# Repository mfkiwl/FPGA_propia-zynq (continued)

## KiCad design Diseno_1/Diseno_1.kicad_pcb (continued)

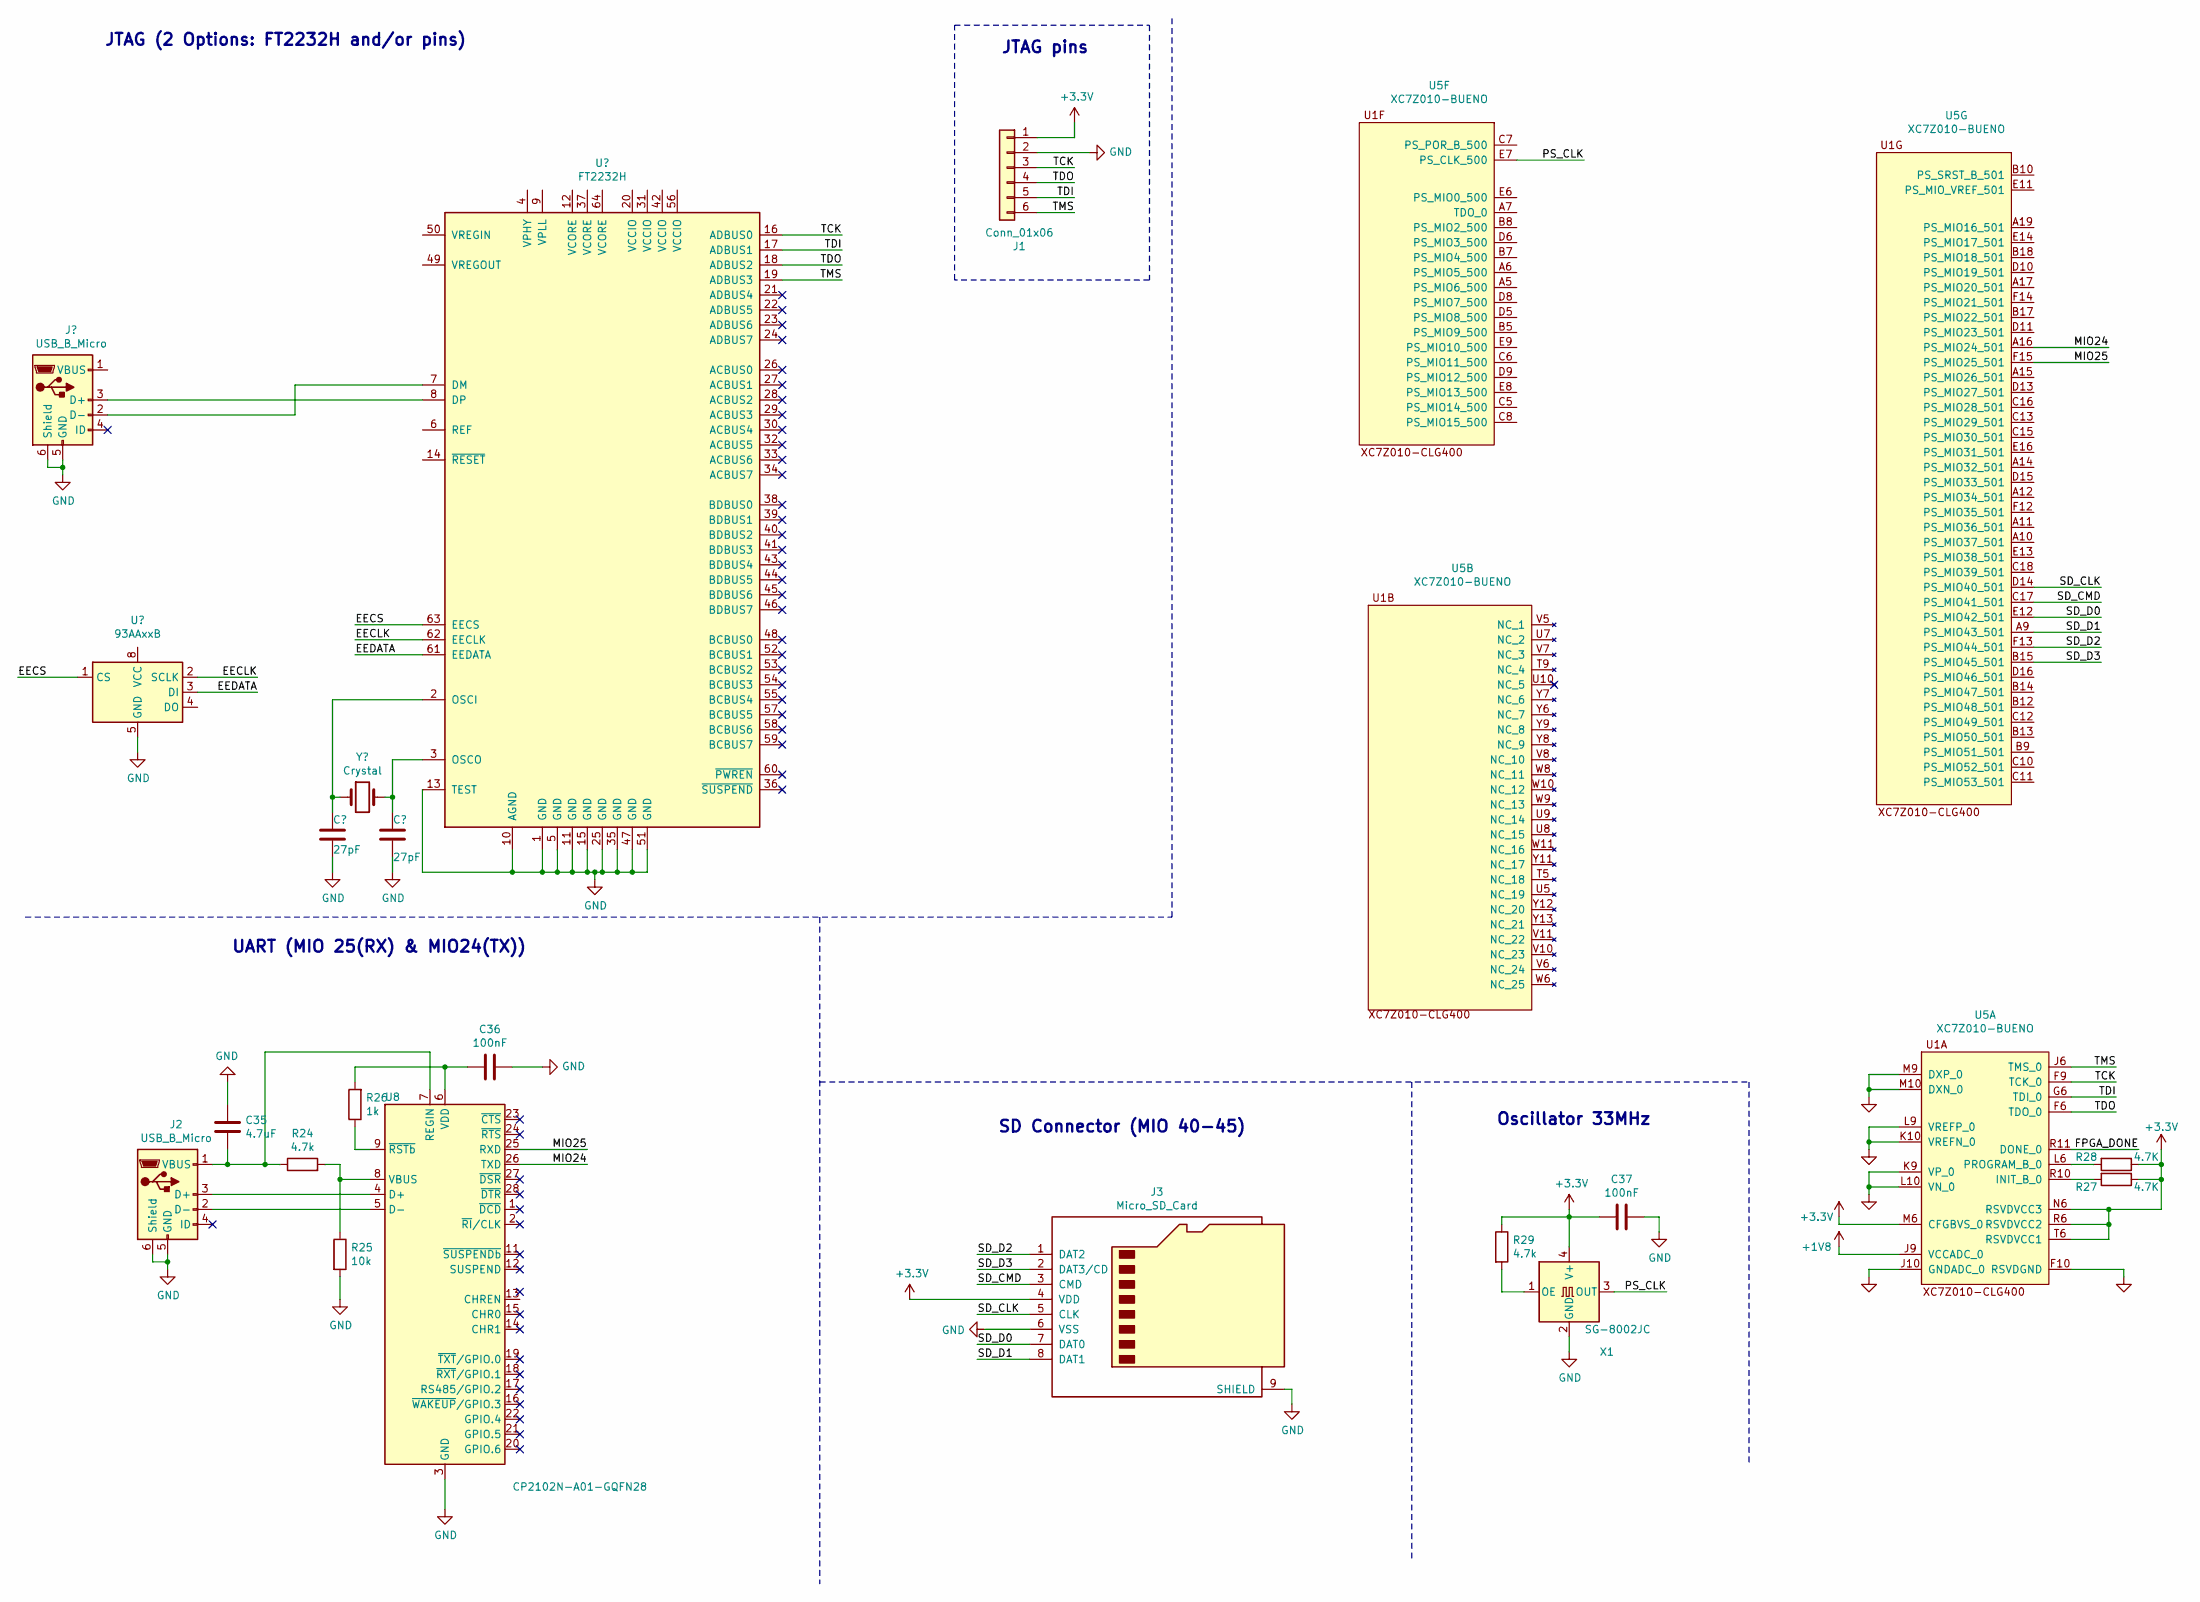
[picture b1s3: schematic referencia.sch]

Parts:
C35: 4.7uF; R_0805_2012Metric
C36: 100nF; R_0805_2012Metric
C37: 100nF; C_0805_2012Metric
J1: Conn_01x06; PinHeader_1x06_P2.54mm_Vertical
J2: USB_B_Micro; USB_Mini-B_Lumberg_2486_01_Horizontal
J3: Micro_SD_Card; microSD_HC_Wuerth_693072010801
R24, R29: 4.7k; R_0805_2012Metric
R25: 10k; R_0805_2012Metric
R26: 1k; R_0805_2012Metric
R27, R28: 4.7K; R_0805_2012Metric
U5: XC7Z010-BUENO; BGA-400_20x20_17.0x17.0mm
U8: CP2102N-A01-GQFN28; QFN-28-1EP_5x5mm_P0.5mm_EP3.35x3.35mm
X1: SG-8002JC; Oscillator_SMD_SeikoEpson_SG8002JC-4Pin_10.5x5.0mm

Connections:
+1V8: U5.J9 (VCCADC_0); also elsewhere on the board
/Entradas y Salidas/BANK34_N17: U5.N17 (IO_L23P_T3_34); also elsewhere on the board
/Entradas y Salidas/BANK34_N18: U5.N18 (IO_L13P_T2_MRCC_34); also elsewhere on the board
/Entradas y Salidas/BANK34_N20: U5.N20 (IO_L14P_T2_SRCC_34); also elsewhere on the board
/Entradas y Salidas/BANK34_P14: U5.P14 (IO_L6P_T0_34); also elsewhere on the board
/Entradas y Salidas/BANK34_P15: U5.P15 (IO_L24P_T3_34); also elsewhere on the board
/Entradas y Salidas/BANK34_P16: U5.P16 (IO_L24N_T3_34); also elsewhere on the board
/Entradas y Salidas/BANK34_P18: U5.P18 (IO_L23N_T3_34); also elsewhere on the board
/Entradas y Salidas/BANK34_P19: U5.P19 (IO_L13N_T2_MRCC_34); also elsewhere on the board
/Entradas y Salidas/BANK34_P20: U5.P20 (IO_L14N_T2_SRCC_34); also elsewhere on the board
/Entradas y Salidas/BANK34_R14: U5.R14 (IO_L6N_T0_VREF_34); also elsewhere on the board
/Entradas y Salidas/BANK34_R16: U5.R16 (IO_L19P_T3_34); also elsewhere on the board
/Entradas y Salidas/BANK34_R17: U5.R17 (IO_L19N_T3_VREF_34); also elsewhere on the board
/Entradas y Salidas/BANK34_R18: U5.R18 (IO_L20N_T3_34); also elsewhere on the board
/Entradas y Salidas/BANK34_R19: U5.R19 (IO_0_34); also elsewhere on the board
/Entradas y Salidas/BANK34_T10: U5.T10 (IO_L1N_0_34); also elsewhere on the board
/Entradas y Salidas/BANK34_T11: U5.T11 (IO_L1P_T0_34); also elsewhere on the board
/Entradas y Salidas/BANK34_T12: U5.T12 (IO_L2P_T0_34); also elsewhere on the board
/Entradas y Salidas/BANK34_T14: U5.T14 (IO_l5P_T0_34); also elsewhere on the board
/Entradas y Salidas/BANK34_T15: U5.T15 (IO_L5N_T0_34); also elsewhere on the board
/Entradas y Salidas/BANK34_T16: U5.T16 (IO_L9P_T1_DQS_34); also elsewhere on the board
/Entradas y Salidas/BANK34_T17: U5.T17 (IO_L20P_T3_34); also elsewhere on the board
/Entradas y Salidas/BANK34_T19: U5.T19 (IO_25_34); also elsewhere on the board
/Entradas y Salidas/BANK34_T20: U5.T20 (IO_L15P_T2_DQS_34); also elsewhere on the board
/Entradas y Salidas/BANK34_U12: U5.U12 (IO_L2N_T0_34); also elsewhere on the board
/Entradas y Salidas/BANK34_U14: U5.U14 (IO_L11P_T1_SRCC_34); also elsewhere on the board
/Entradas y Salidas/BANK34_U15: U5.U15 (IO_L11N_T1_SRCC_34); also elsewhere on the board
/Entradas y Salidas/BANK34_U17: U5.U17 (IO_L9N_T1_DQS_34); also elsewhere on the board
/Entradas y Salidas/BANK34_U18: U5.U18 (IO_L12P_T1_MRCC_34); also elsewhere on the board
/Entradas y Salidas/BANK34_U19: U5.U19 (IO_L12N_T1_MRCC_34); also elsewhere on the board
/Entradas y Salidas/BANK34_U20: U5.U20 (IO_L5N_T2_DQS_34); also elsewhere on the board
/Entradas y Salidas/BANK34_V12: U5.V12 (IO_L4P_T0_34); also elsewhere on the board
/Entradas y Salidas/BANK34_V13: U5.V13 (IO_L3N_T0_DQS_34); also elsewhere on the board
/Entradas y Salidas/BANK34_V15: U5.V15 (IO_L10P_T1_34); also elsewhere on the board
/Entradas y Salidas/BANK34_V16: U5.V16 (IO_L18P_T2_34); also elsewhere on the board
/Entradas y Salidas/BANK34_V17: U5.V17 (IO_L21P_T3_VREF_34); also elsewhere on the board
/Entradas y Salidas/BANK34_V18: U5.V18 (IO_L21N_T3_DQS_34); also elsewhere on the board
/Entradas y Salidas/BANK34_V20: U5.V20 (IO_L6P_T2_34); also elsewhere on the board
/Entradas y Salidas/BANK34_W13: U5.W13 (IO_L4N_T0_34); also elsewhere on the board
/Entradas y Salidas/BANK34_W14: U5.W14 (IO_L8P_T1_34); also elsewhere on the board
/Entradas y Salidas/BANK34_W15: U5.W15 (IO_L10N_T1_34); also elsewhere on the board
/Entradas y Salidas/BANK34_W16: U5.W16 (IO_L18N_T2_34); also elsewhere on the board
/Entradas y Salidas/BANK34_W18: U5.W18 (IO_L22P_T3_34); also elsewhere on the board
/Entradas y Salidas/BANK34_W19: U5.W19 (IO_L22N_T3_34); also elsewhere on the board
/Entradas y Salidas/BANK34_W20: U5.W20 (IO_L6N_T2_34); also elsewhere on the board
/Entradas y Salidas/BANK34_Y14: U5.Y14 (IO_L8N_T1_34); also elsewhere on the board
/Entradas y Salidas/BANK34_Y16: U5.Y16 (IO_L7P_T1_34); also elsewhere on the board
/Entradas y Salidas/BANK34_Y17: U5.Y17 (IO_L7N_T1_34); also elsewhere on the board
/Entradas y Salidas/BANK34_Y18: U5.Y18 (IO_L17P_T2_34); also elsewhere on the board
/Entradas y Salidas/BANK34_Y19: U5.Y19 (IO_L17N_T2_34); also elsewhere on the board
/Entradas y Salidas/BANK35_A20: U5.A20 (IO_L2N_T0_AD8N_35); also elsewhere on the board
/Entradas y Salidas/BANK35_B19: U5.B19 (IO_L2P_T0_AD8P_35); also elsewhere on the board
/Entradas y Salidas/BANK35_B20: U5.B20 (IO_L1N_T0_AD0P_35); also elsewhere on the board
/Entradas y Salidas/BANK35_C20: U5.C20 (IO_L1P_T0_AD0P_35); also elsewhere on the board
/Entradas y Salidas/BANK35_D18: U5.D18 (IO_L3N_T0_DQS_AD1N_35); also elsewhere on the board
/Entradas y Salidas/BANK35_D19: U5.D19 (IO_L4P_T0_35); also elsewhere on the board
/Entradas y Salidas/BANK35_D20: U5.D20 (IO_L4N_T0_35); also elsewhere on the board
/Entradas y Salidas/BANK35_E17: U5.E17 (IO_L3P_T0_DQS_AD1P_35); also elsewhere on the board
/Entradas y Salidas/BANK35_E18: U5.E18 (IO_L5P_T0_AD9P_35); also elsewhere on the board
/Entradas y Salidas/BANK35_E19: U5.E19 (IO_L5N_T0_AD9N_35); also elsewhere on the board
/Entradas y Salidas/BANK35_F16: U5.F16 (IO_L6P_T0_35); also elsewhere on the board
/Entradas y Salidas/BANK35_F17: U5.F17 (IO_L6N_T0_VREF_35); also elsewhere on the board
/Entradas y Salidas/BANK35_F19: U5.F19 (IO_L15P_T2_DQS_AD12P_35); also elsewhere on the board
/Entradas y Salidas/BANK35_F20: U5.F20 (IO_L15N_T2_DQS_AD12N_35); also elsewhere on the board
/Entradas y Salidas/BANK35_G14: U5.G14 (IO_0_35); also elsewhere on the board
/Entradas y Salidas/BANK35_G15: U5.G15 (IO_L19N_T3_VREF_35); also elsewhere on the board
/Entradas y Salidas/BANK35_G17: U5.G17 (IO_L16P_T2_35); also elsewhere on the board
/Entradas y Salidas/BANK35_G18: U5.G18 (IO_L16N_T2_35); also elsewhere on the board
/Entradas y Salidas/BANK35_G19: U5.G19 (IO_L18P_T2_AD13P_35); also elsewhere on the board
/Entradas y Salidas/BANK35_G20: U5.G20 (IO_L18N_T2_AD13N_35); also elsewhere on the board
/Entradas y Salidas/BANK35_H15: U5.H15 (IO_L19P_T3_35); also elsewhere on the board
/Entradas y Salidas/BANK35_H16: U5.H16 (IO_L13P_T2_MRCC_35); also elsewhere on the board
/Entradas y Salidas/BANK35_H17: U5.H17 (IO_L13N_T2_MRCC_35); also elsewhere on the board
/Entradas y Salidas/BANK35_H18: U5.H18 (IO_L14N_T2_AD4N_SRCC_35); also elsewhere on the board
/Entradas y Salidas/BANK35_H20: U5.H20 (IO_L17N_T2_AD5N_35); also elsewhere on the board
/Entradas y Salidas/BANK35_J14: U5.J14 (IO_L20N_T3_AD6N_35); also elsewhere on the board
/Entradas y Salidas/BANK35_J15: U5.J15 (IO_25_35); also elsewhere on the board
/Entradas y Salidas/BANK35_J16: U5.J16 (IO_L24N_T3_AD15N_35); also elsewhere on the board
/Entradas y Salidas/BANK35_J18: U5.J18 (IO_L14P_T2_AD4P_SRCC_35); also elsewhere on the board
/Entradas y Salidas/BANK35_J19: U5.J19 (IO_L10N_AD11N_35); also elsewhere on the board
/Entradas y Salidas/BANK35_J20: U5.J20 (IO_L17P_T2_AD5P_35); also elsewhere on the board
/Entradas y Salidas/BANK35_K14: U5.K14 (IO_L20P_T3_AD6P_35); also elsewhere on the board
/Entradas y Salidas/BANK35_K16: U5.K16 (IO_L24P_T3_AD15P_35); also elsewhere on the board
/Entradas y Salidas/BANK35_K17: U5.K17 (IO_L12P_T1_MRCC_35); also elsewhere on the board
/Entradas y Salidas/BANK35_K18: U5.K18 (IO_L12N_T1_MRCC_35); also elsewhere on the board
/Entradas y Salidas/BANK35_K19: U5.K19 (IO_L10P_T1_AD11P_35); also elsewhere on the board
/Entradas y Salidas/BANK35_L14: U5.L14 (IO_L22P_T3_AD7P_35); also elsewhere on the board
/Entradas y Salidas/BANK35_L15: U5.L15 (IO_L22N_T3_AD7N_35); also elsewhere on the board
/Entradas y Salidas/BANK35_L16: U5.L16 (IO_L11P_T1_SRCC_35); also elsewhere on the board
/Entradas y Salidas/BANK35_L17: U5.L17 (IO_L11N_T1_SRCC_35); also elsewhere on the board
/Entradas y Salidas/BANK35_L19: U5.L19 (IO_L9P_T1_DQS_AD3P_35); also elsewhere on the board
/Entradas y Salidas/BANK35_L20: U5.L20 (IO_L9N_T1_DQS_AD3N_35); also elsewhere on the board
/Entradas y Salidas/BANK35_M14: U5.M14 (IO_L23P_T3_35); also elsewhere on the board
/Entradas y Salidas/BANK35_M15: U5.M15 (IO_L23N_T3_35); also elsewhere on the board
/Entradas y Salidas/BANK35_M17: U5.M17 (IO_L8P_T1_AD10P_35); also elsewhere on the board
/Entradas y Salidas/BANK35_M18: U5.M18 (IO_L8N_T1_AD10N_35); also elsewhere on the board
/Entradas y Salidas/BANK35_M19: U5.M19 (IO_L7P_T1_AD2P_35); also elsewhere on the board
/Entradas y Salidas/BANK35_M20: U5.M20 (IO_L7N_T1_AD2N_35); also elsewhere on the board
/Entradas y Salidas/BANK35_N15: U5.N15 (IO_L21P_T3_DQS_AD14P_35); also elsewhere on the board
/Entradas y Salidas/BANK35_N16: U5.N16 (IO_L21N_T3_DQS_AD14N_35); also elsewhere on the board
/Referencias y MIOs/MIO24: U5.A16 (PS_MIO24_501), U8.26 (TXD)
/Referencias y MIOs/MIO25: U5.F15 (PS_MIO25_501), U8.25 (RXD)
/Referencias y MIOs/PS_CLK: U5.E7 (PS_CLK_500), X1.3 (OUT)
/Referencias y MIOs/SD_CLK: J3.5 (CLK), U5.D14 (PS_MIO40_501)
/Referencias y MIOs/SD_CMD: J3.3 (CMD), U5.C17 (PS_MIO41_501)
/Referencias y MIOs/SD_D0: J3.7 (DAT0), U5.E12 (PS_MIO42_501)
/Referencias y MIOs/SD_D1: J3.8 (DAT1), U5.A9 (PS_MIO43_501)
/Referencias y MIOs/SD_D2: J3.1 (DAT2), U5.F13 (PS_MIO44_501)
/Referencias y MIOs/SD_D3: J3.2 (DAT3/CD), U5.B15 (PS_MIO45_501)
/Referencias y MIOs/TCK: J1.3, U5.F9 (TCK_0)
/Referencias y MIOs/TDI: J1.5, U5.G6 (TDI_0)
/Referencias y MIOs/TDO: J1.4, U5.F6 (TDO_0)
/Referencias y MIOs/TMS: J1.6, U5.J6 (TMS_0)
GND: C35.1, C36.1, C37.1, J1.2, J2.5 (GND), J2.6 (Shield), J3.6 (VSS), J3.9 (SHIELD), R25.2, U5.F10 (RSVDGND), U5.J10 (GNDADC_0), U5.K9 (VP_0), U5.K10 (VREFN_0), U5.L9 (VREFP_0), U5.L10 (VN_0), U5.M9 (DXP_0), U5.M10 (DXN_0), U5.U13 (IO_L3P_T0_DQS_PUDC_B_34), U8.3 (GND), U8.29 (GND), X1.2 (GND); also elsewhere on the board
unnamed: C35.2, J2.1 (VBUS), R24.1, U8.7 (REGIN)
unnamed: C36.2, R26.2, U8.6 (VDD)
unnamed: J2.2 (D-), U8.5 (D-)
unnamed: J2.3 (D+), U8.4 (D+)
unnamed: R24.2, R25.1, U8.8 (VBUS)
unnamed: R26.1, U8.9 (~RSTb)
unnamed: R27.2, U5.R10 (INIT_B_0)
unnamed: R28.2, U5.L6 (PROGRAM_B_0)
unnamed: R29.2, X1.1 (OE)

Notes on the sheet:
UART (MIO 25(RX) & MIO24(TX))
SD Connector (MIO 40-45)
Oscillator 33MHz
JTAG pins
JTAG (2 Options: FT2232H and/or pins)

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
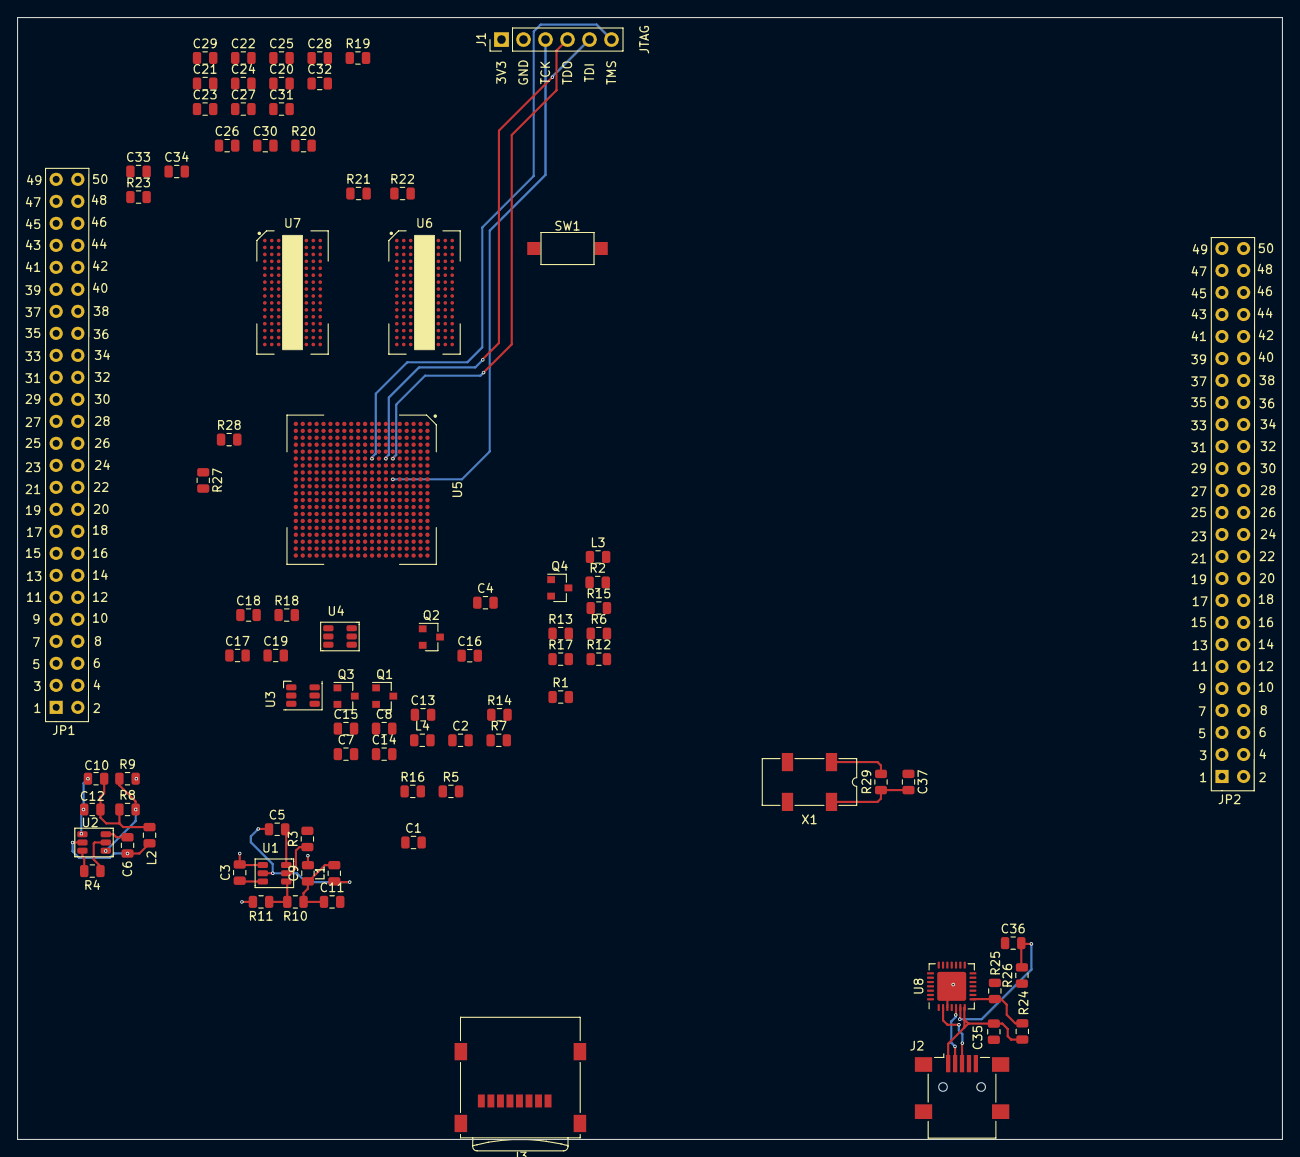
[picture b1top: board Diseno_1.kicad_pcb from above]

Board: 2 copper layers, 146.1 x 129.5 mm, 89 parts (0 on the bottom side), 225 nets.

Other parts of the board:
JP1, JP2: Pines_Bloque_50; PINES_50_NUMERO
SW1: SW_Push; SW_SPST_CK_RS282G05A3

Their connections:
/Entradas y Salidas/BANK34_N17: JP1.42; also elsewhere on the board
/Entradas y Salidas/BANK34_N18: JP1.2; also elsewhere on the board
/Entradas y Salidas/BANK34_N20: JP1.6; also elsewhere on the board
/Entradas y Salidas/BANK34_P14: JP1.23; also elsewhere on the board
/Entradas y Salidas/BANK34_P15: JP1.46; also elsewhere on the board
/Entradas y Salidas/BANK34_P16: JP1.48; also elsewhere on the board
/Entradas y Salidas/BANK34_P18: JP1.44; also elsewhere on the board
/Entradas y Salidas/BANK34_P19: JP1.4; also elsewhere on the board
/Entradas y Salidas/BANK34_P20: JP1.8; also elsewhere on the board
/Entradas y Salidas/BANK34_R14: JP1.25; also elsewhere on the board
/Entradas y Salidas/BANK34_R16: JP1.26; also elsewhere on the board
/Entradas y Salidas/BANK34_R17: JP1.28; also elsewhere on the board
/Entradas y Salidas/BANK34_R18: JP1.32; also elsewhere on the board
/Entradas y Salidas/BANK34_R19: JP1.1; also elsewhere on the board
/Entradas y Salidas/BANK34_T10: JP1.5; also elsewhere on the board
/Entradas y Salidas/BANK34_T11: JP1.3; also elsewhere on the board
/Entradas y Salidas/BANK34_T12: JP1.7; also elsewhere on the board
/Entradas y Salidas/BANK34_T14: JP1.19; also elsewhere on the board
/Entradas y Salidas/BANK34_T15: JP1.21; also elsewhere on the board
/Entradas y Salidas/BANK34_T16: JP1.35; also elsewhere on the board
/Entradas y Salidas/BANK34_T17: JP1.30; also elsewhere on the board
/Entradas y Salidas/BANK34_T19: JP1.50; also elsewhere on the board
/Entradas y Salidas/BANK34_T20: JP1.10; also elsewhere on the board
/Entradas y Salidas/BANK34_U12: JP1.9; also elsewhere on the board
/Entradas y Salidas/BANK34_U14: JP1.43; also elsewhere on the board
/Entradas y Salidas/BANK34_U15: JP1.45; also elsewhere on the board
/Entradas y Salidas/BANK34_U17: JP1.37; also elsewhere on the board
/Entradas y Salidas/BANK34_U18: JP1.47; also elsewhere on the board
/Entradas y Salidas/BANK34_U19: JP1.49; also elsewhere on the board
/Entradas y Salidas/BANK34_U20: JP1.12; also elsewhere on the board
/Entradas y Salidas/BANK34_V12: JP1.15; also elsewhere on the board
/Entradas y Salidas/BANK34_V13: JP1.13; also elsewhere on the board
/Entradas y Salidas/BANK34_V15: JP1.39; also elsewhere on the board
/Entradas y Salidas/BANK34_V16: JP1.22; also elsewhere on the board
/Entradas y Salidas/BANK34_V17: JP1.34; also elsewhere on the board
/Entradas y Salidas/BANK34_V18: JP1.36; also elsewhere on the board
/Entradas y Salidas/BANK34_V20: JP1.14; also elsewhere on the board
/Entradas y Salidas/BANK34_W13: JP1.17; also elsewhere on the board
/Entradas y Salidas/BANK34_W14: JP1.31; also elsewhere on the board
/Entradas y Salidas/BANK34_W15: JP1.41; also elsewhere on the board
/Entradas y Salidas/BANK34_W16: JP1.24; also elsewhere on the board
/Entradas y Salidas/BANK34_W18: JP1.38; also elsewhere on the board
/Entradas y Salidas/BANK34_W19: JP1.40; also elsewhere on the board
/Entradas y Salidas/BANK34_W20: JP1.16; also elsewhere on the board
/Entradas y Salidas/BANK34_Y14: JP1.33; also elsewhere on the board
/Entradas y Salidas/BANK34_Y16: JP1.27; also elsewhere on the board
/Entradas y Salidas/BANK34_Y17: JP1.29; also elsewhere on the board
/Entradas y Salidas/BANK34_Y18: JP1.18; also elsewhere on the board
/Entradas y Salidas/BANK34_Y19: JP1.20; also elsewhere on the board
/Entradas y Salidas/BANK35_A20: JP2.9; also elsewhere on the board
/Entradas y Salidas/BANK35_B19: JP2.7; also elsewhere on the board
/Entradas y Salidas/BANK35_B20: JP2.5; also elsewhere on the board
/Entradas y Salidas/BANK35_C20: JP2.3; also elsewhere on the board
/Entradas y Salidas/BANK35_D18: JP2.13; also elsewhere on the board
/Entradas y Salidas/BANK35_D19: JP2.15; also elsewhere on the board
/Entradas y Salidas/BANK35_D20: JP2.17; also elsewhere on the board
/Entradas y Salidas/BANK35_E17: JP2.11; also elsewhere on the board
/Entradas y Salidas/BANK35_E18: JP2.19; also elsewhere on the board
/Entradas y Salidas/BANK35_E19: JP2.21; also elsewhere on the board
/Entradas y Salidas/BANK35_F16: JP2.23; also elsewhere on the board
/Entradas y Salidas/BANK35_F17: JP2.25; also elsewhere on the board
/Entradas y Salidas/BANK35_F19: JP2.10; also elsewhere on the board
/Entradas y Salidas/BANK35_F20: JP2.12; also elsewhere on the board
/Entradas y Salidas/BANK35_G14: JP2.1; also elsewhere on the board
/Entradas y Salidas/BANK35_G15: JP2.28; also elsewhere on the board
/Entradas y Salidas/BANK35_G17: JP2.14; also elsewhere on the board
/Entradas y Salidas/BANK35_G18: JP2.16; also elsewhere on the board
/Entradas y Salidas/BANK35_G19: JP2.22; also elsewhere on the board
/Entradas y Salidas/BANK35_G20: JP2.24; also elsewhere on the board
/Entradas y Salidas/BANK35_H15: JP2.26; also elsewhere on the board
/Entradas y Salidas/BANK35_H16: JP2.2; also elsewhere on the board
/Entradas y Salidas/BANK35_H17: JP2.4; also elsewhere on the board
/Entradas y Salidas/BANK35_H18: JP2.8; also elsewhere on the board
/Entradas y Salidas/BANK35_H20: JP2.20; also elsewhere on the board
/Entradas y Salidas/BANK35_J14: JP2.32; also elsewhere on the board
/Entradas y Salidas/BANK35_J15: JP2.50; also elsewhere on the board
/Entradas y Salidas/BANK35_J16: JP2.48; also elsewhere on the board
/Entradas y Salidas/BANK35_J18: JP2.6; also elsewhere on the board
/Entradas y Salidas/BANK35_J19: JP2.41; also elsewhere on the board
/Entradas y Salidas/BANK35_J20: JP2.18; also elsewhere on the board
/Entradas y Salidas/BANK35_K14: JP2.30; also elsewhere on the board
/Entradas y Salidas/BANK35_K16: JP2.46; also elsewhere on the board
/Entradas y Salidas/BANK35_K17: JP2.47; also elsewhere on the board
/Entradas y Salidas/BANK35_K18: JP2.49; also elsewhere on the board
/Entradas y Salidas/BANK35_K19: JP2.39; also elsewhere on the board
/Entradas y Salidas/BANK35_L14: JP2.38; also elsewhere on the board
/Entradas y Salidas/BANK35_L15: JP2.40; also elsewhere on the board
/Entradas y Salidas/BANK35_L16: JP2.43; also elsewhere on the board
/Entradas y Salidas/BANK35_L17: JP2.45; also elsewhere on the board
/Entradas y Salidas/BANK35_L19: JP2.35; also elsewhere on the board
/Entradas y Salidas/BANK35_L20: JP2.37; also elsewhere on the board
/Entradas y Salidas/BANK35_M14: JP2.42; also elsewhere on the board
/Entradas y Salidas/BANK35_M15: JP2.44; also elsewhere on the board
/Entradas y Salidas/BANK35_M17: JP2.31; also elsewhere on the board
/Entradas y Salidas/BANK35_M18: JP2.33; also elsewhere on the board
/Entradas y Salidas/BANK35_M19: JP2.27; also elsewhere on the board
/Entradas y Salidas/BANK35_M20: JP2.29; also elsewhere on the board
/Entradas y Salidas/BANK35_N15: JP2.34; also elsewhere on the board
/Entradas y Salidas/BANK35_N16: JP2.36; also elsewhere on the board

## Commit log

2020-12-28 actualización memoria ram en README
2020-12-28 extraer cosas in/utiles
2020-12-31 actualizacion
2021-01-02 muchas cosas
